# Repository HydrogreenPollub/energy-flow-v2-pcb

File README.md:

## Energy flow PCB

CADLAB preview: [link](https://cadlab.io/project/27708)

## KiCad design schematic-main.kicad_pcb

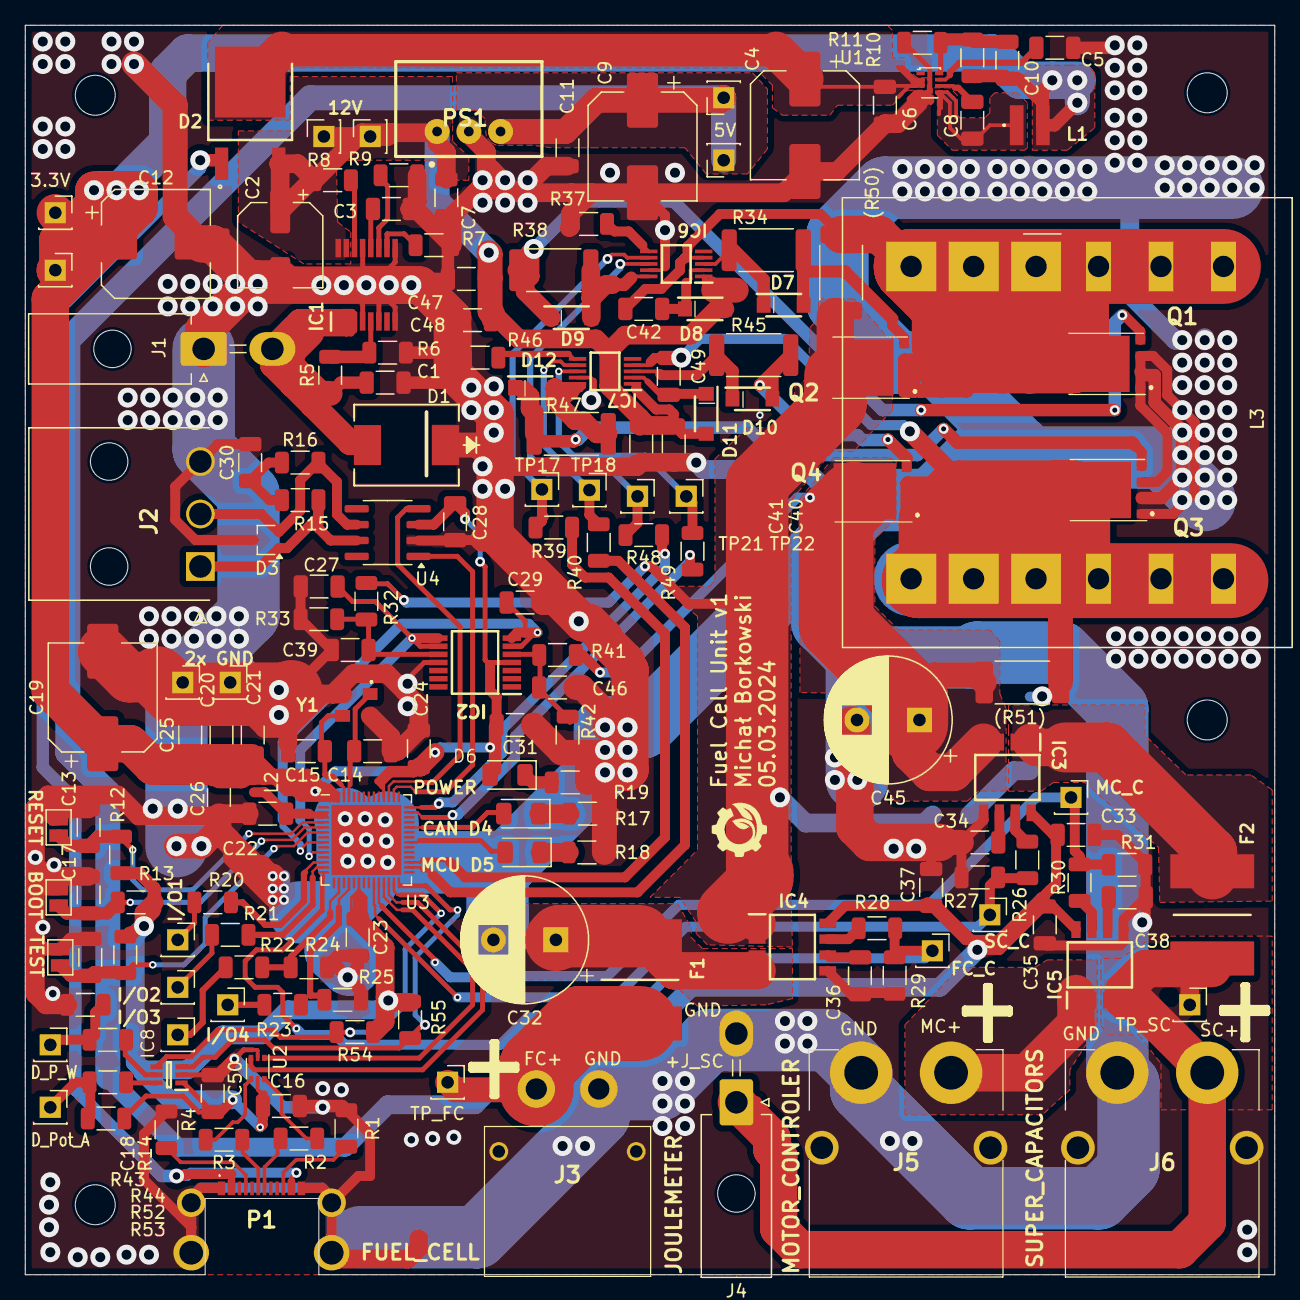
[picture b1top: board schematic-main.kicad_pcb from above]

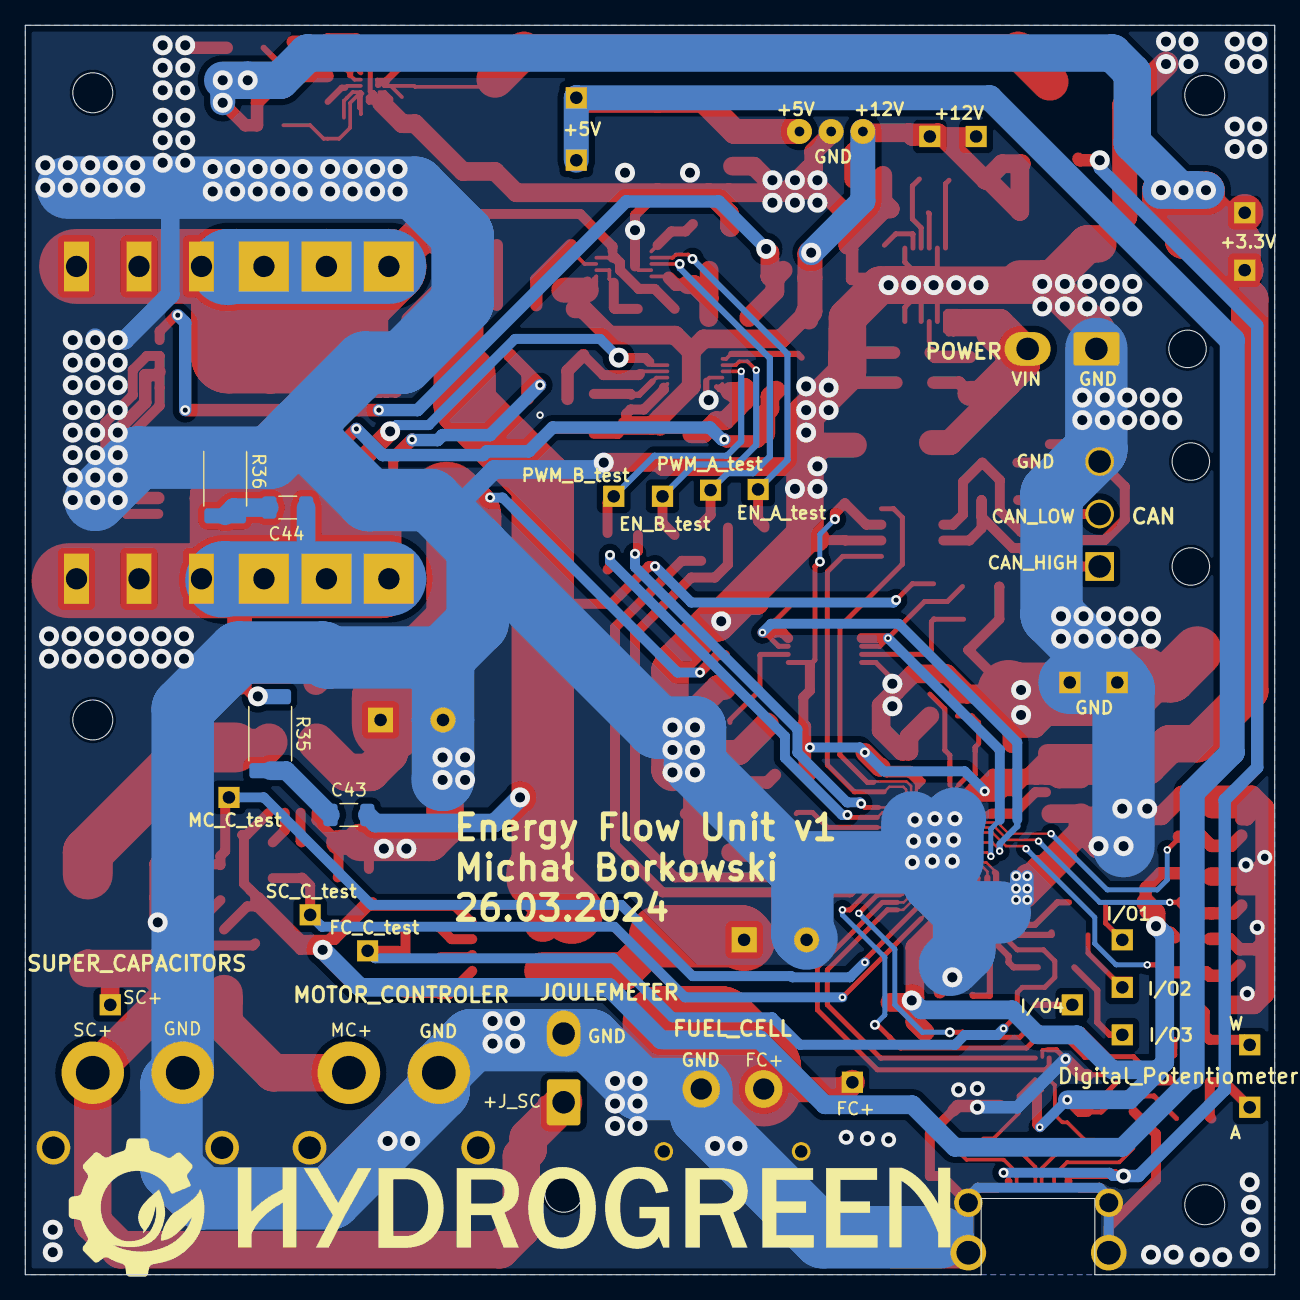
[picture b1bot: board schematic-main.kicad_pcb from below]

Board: 2 copper layers, 100.0 x 100.0 mm, 173 parts (4 on the bottom side), 96 nets.

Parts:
3.3V: +3.3V; PinSocket_1x01_P2.54mm_Vertical
5V: +5V; PinSocket_1x01_P2.54mm_Vertical
12V: +12V; PinSocket_1x01_P2.54mm_Vertical
 D6: LED; D_1206_3216Metric
(R50), (R51): 0R; R_2512_6332Metric_Pad1.40x3.35mm_HandSolder
BOOT: SolderJumper_2_Open; SolderJumper-2_P1.3mm_Open_Pad1.0x1.5mm
C1, C13, C17, C18, C20, C25: 1u; C_1206_3216Metric
C2: 47u; CP_Elec_6.3x7.7
C3: 2n7; C_1206_3216Metric
C4, C9, C19: 10u; CP_Elec_8x10.5
C5: 33n; C_1206_3216Metric
C6, C7, C8, C11, C16, C21, C22, C23, C24, C28, C31, C33, C35, C37, C50: 100n; C_1206_3216Metric
C10: 47p; C_1206_3216Metric
C12: 100u; CP_Elec_8x10.5
C14, C15: 12p; C_1206_3216Metric
C26, C41, C48: 10n; C_1206_3216Metric
C27, C29, C30: 4n7; C_1206_3216Metric
C32, C45: 100u 100V; CP_Radial_D10.0mm_P5.00mm
C34, C36, C38, C39, C46: 1n; C_1206_3216Metric
C40, C47: 470n; C_1206_3216Metric
C42, C49: 100n 100V; C_1206_3216Metric
C43, C44: 100p 100V; C_1206_3216Metric
CAN D4: LED; D_1206_3216Metric
D1: TPSMC30CA; TPSMCSeries_LTF
D2: MBRD20100CT-13; TO252_(DPAK)_1
D3: SP0502BAJT; SOT-323_SC-70
D7, D8, D9, D10, D11, D12: SKL120-AQ; SODFL3718X170N
D_P_W: D_Pot_W; PinSocket_1x01_P2.54mm_Vertical
D_Pot_A: D_Pot_A; PinSocket_1x01_P2.54mm_Vertical
F1, F2: 5A; FUSC8664X180N
FC_C: FC_C_test; PinSocket_1x01_P2.54mm_Vertical
I/O1: I/O 1; PinSocket_1x01_P2.54mm_Vertical
I/O2: I/O 2; PinSocket_1x01_P2.54mm_Vertical
I/O3: I/O 3; PinSocket_1x01_P2.54mm_Vertical
I/O4: I/O 4; PinSocket_1x01_P2.54mm_Vertical
IC1: LM76202QPWPRQ1; SOP65P640X120-17N
IC2: AD8544ARUZ-REEL; SOP65P640X120-14N
IC3, IC5: ACHS-7123-000E; SOIC127P606X204-8N
IC4: ACHS-7121-000E; SOIC127P606X204-8N
IC6, IC7: LM5106MMX_NOPB; SOP50P490X110-10N
IC8: MCP4018T-503E_LT; SOT65P210X110-6N
J1: Battery converter; Molex_Mini-Fit_Jr_5569-02A2_2x01_P4.20mm_Horizontal
J2: CAN; 39303035
J3: FUEL CELL; XT30PWF
J4: Joulemeter; Molex_Mini-Fit_Jr_5569-02A2_2x01_P4.20mm_Horizontal
J5: MOTOR CONTROLER; XT60PWM
J6: SUPER CAPACITORS; XT60PWM
L1: 4u7; SRN3015TA4R7M
L2: 2n; L_0402_1005Metric
L3: 700uH; L_Wurth_WE-HCFT-2012_LeadDiameter1.2mm
MCU D5: LED; D_1206_3216Metric
MC_C: MC_C_test; PinSocket_1x01_P2.54mm_Vertical
P1: USB_C_Plug_USB2.0; 2169900002
PS1: TSR_1-2450; TSR-1-24120
Q1, Q2, Q3, Q4: CSD19531Q5AT
R1, R4: 5k1; R_1206_3216Metric
R2, R3: 0; R_1206_3216Metric
R5: 180k; R_1206_3216Metric
R6: 12k; R_1206_3216Metric
R7, R8: 100k; R_1206_3216Metric
R9: 56k; R_1206_3216Metric
R10: 32k; R_1206_3216Metric
R11, R12, R13, R14, R24, R25, R26, R28, R30, R37, R43, R44, R46, R52, R53: 10k; R_1206_3216Metric
R15, R16: 60; R_1206_3216Metric
R17, R18, R19, R20, R21: 1k; R_1206_3216Metric
R22, R23: 100R; R_1206_3216Metric
R27, R29, R31: 20k; R_1206_3216Metric
R32: 68k; R_1206_3216Metric
R33: 3k9; R_1206_3216Metric
R34, R38, R45, R47: 10R 2W; R_2512_6332Metric
R35, R36: 100R 0,5W; R_2512_6332Metric
R39, R40, R48, R49: 200R; R_1206_3216Metric
R41: 62k; R_1206_3216Metric
R42: 4k7; R_1206_3216Metric
R54, R55: 4,7k; R_1206_3216Metric
RESET: SolderJumper_2_Open; SolderJumper-2_P1.3mm_Open_Pad1.0x1.5mm
SC_C: SC_C_test; PinSocket_1x01_P2.54mm_Vertical
TEST: SolderJumper_2_Open; SolderJumper-2_P1.3mm_Open_Pad1.0x1.5mm
TP1, TP2: GND; PinSocket_1x01_P2.54mm_Vertical
TP3: +12V; PinSocket_1x01_P2.54mm_Vertical
TP5: +5V; PinSocket_1x01_P2.54mm_Vertical
TP8: +3.3V; PinSocket_1x01_P2.54mm_Vertical
TP17: EN A test; PinSocket_1x01_P2.54mm_Vertical
TP18: PWM A test; PinSocket_1x01_P2.54mm_Vertical
TP21: EN B test; PinSocket_1x01_P2.54mm_Vertical
TP22: PWM B test; PinSocket_1x01_P2.54mm_Vertical
TP_FC: FC test; PinSocket_1x01_P2.54mm_Vertical
TP_SC: SC test; PinSocket_1x01_P2.54mm_Vertical
U1: TPS62933; SOT-583-8
U2: USBLC6-2P6; SOT-666
U3: ESP32-S3FN8; QFN-56-1EP_7x7mm_P0.4mm_EP5.6x5.6mm
U4: SN65HVD232; SOIC-8_3.9x4.9mm_P1.27mm
Y1: Crystal_GND24; KC3225K400000C1GE00

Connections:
+3.3V: 3.3V.1, D6.2 (A), C10.1, C12.1, C16.1, C19.1, C20.1, C21.1, C23.1, C24.1, C25.1, C26.1, C28.1, C31.1, C50.1, IC2.4 (V+), IC8.1 (VDD), L1.2, L2.1, R10.1, R12.2, R13.2, R14.2, R53.1, R54.1, R55.1, TP8.1, U2.5 (VBUS), U3.20 (VDD3P3_RTC), U3.46 (VDD3P3_CPU), U3.55 (VDDA), U3.56 (VDDA), U4.3 (VCC)
+5V: 5V.1, C9.1, C11.1, C33.1, C35.1, C37.1, IC3.8 (VDD), IC4.8 (VDD), IC5.8 (VDD), PS1.3 (VOUT+), TP5.1
+12V: 12V.1, C2.1, C7.1, C40.1, C41.1, C47.1, C48.1, D2.2, D8.2 (A), D11.2 (A), IC1.15 (OUT_1), IC1.16 (OUT_2), IC6.1 (VDD), IC7.1 (VDD), PS1.1 (VIN+), R8.1, TP3.1
/Converter/Bootstrap_A: (R50).2, C42.2, IC6.4 (HS), L3.1, Q1.5 (D_1), Q1.6 (D_2), Q1.7 (D_3), Q1.8 (D_4), Q1.9 (D_5), Q2.1 (S_1), Q2.2 (S_2), Q2.3 (S_3)
/Converter/Bootstrap_B: (R51).1, C44.1, C49.2, IC7.4 (HS), L3.2, Q3.5 (D_1), Q3.6 (D_2), Q3.7 (D_3), Q3.8 (D_4), Q3.9 (D_5), Q4.1 (S_1), Q4.2 (S_2), Q4.3 (S_3), R35.1
/Converter/Converter_ON_A_MCU: R39.1, U3.31 (SPIWP/GPIO28)
/Converter/Converter_ON_B_MCU: R48.1, U3.42 (GPIO37)
/Converter/Converter_PWM_A_MCU: R40.2, U3.30 (SPIHD/GPIO27)
/Converter/Converter_PWM_B_MCU: R49.2, U3.41 (GPIO36)
/Converter/FC+: F1.1, J3.2, TP_FC.1
/Converter/FC_V: C39.1, IC2.10 (+IN_C), R32.1, R33.2
/Converter/FC_c1: C32.1, F1.2, IC4.3 (IP-_1), IC4.4 (IP-_2)
/Converter/FC_c2: (R50).1, C43.1, IC4.1 (IP+_1), IC4.2 (IP+_2), Q2.5 (D_1), Q2.6 (D_2), Q2.7 (D_3), Q2.8 (D_4), Q2.9 (D_5), R32.2
/Converter/FC_c_MCU: FC_C.1, R28.1, R29.2, U3.14 (GPIO9/ADC1_CH8)
/Converter/High_mosfet_A: D7.2 (A), Q2.4 (G), R34.2
/Converter/High_mosfet_B: D10.2 (A), Q4.4 (G), R45.2
/Converter/Low_mosfet_A: D9.1 (K), Q1.4 (G), R38.1
/Converter/Low_mosfet_B: D12.1 (K), Q3.4 (G), R47.1
/Converter/MC_c1: F2.1, IC5.3 (IP-_1), IC5.4 (IP-_2), J4.1, J6.1, TP_SC.1
/Converter/MC_c2: IC5.1 (IP+_1), IC5.2 (IP+_2), J5.1
/Converter/MC_c_MCU: MC_C.1, R30.1, R31.2, U3.24 (GPIO18/ADC2_CH7)
/Converter/SC_V: C46.1, IC2.5 (+IN_B), R41.1, R42.2
/Converter/SC_c1: (R51).2, C45.1, IC3.3 (IP-_1), IC3.4 (IP-_2), Q4.5 (D_1), Q4.6 (D_2), Q4.7 (D_3), Q4.8 (D_4), Q4.9 (D_5), R41.2
/Converter/SC_c2: F2.2, IC3.1 (IP+_1), IC3.2 (IP+_2)
/Converter/SC_c_MCU: R26.1, R27.2, SC_C.1, U3.23 (GPIO17/ADC2_CH6)
/IO/CANH: D3.1 (K), J2.1, R15.2, U4.7 (CANH)
/IO/CANL: D3.2 (K), J2.2, R16.2, U4.6 (CANL)
/IO/CAN_RX: U3.44 (MTCK/JTAG/GPIO39), U4.1 (D)
/IO/CAN_TX: U3.45 (MTDO/JTAG/GPIO40), U4.4 (R)
/IO/FC_Voltage_MCU: C27.1, IC2.8 (OUT_C), IC2.9 (-IN_C), U3.10 (GPIO5/ADC1_CH4)
/IO/I/O_1_MCU: R20.2, U3.12 (GPIO7/ADC1_CH6)
/IO/I/O_2_MCU: R21.2, U3.13 (GPIO8/ADC1_CH7)
/IO/I/O_3_MCU: R22.2, R24.1, U3.16 (GPIO11/ADC2_CH0)
/IO/I/O_4_MCU: R23.2, R25.1, U3.18 (GPIO13/ADC2_CH2)
/IO/LED_CAN_STATUS: CAN D4.2 (A), U3.38 (GPIO33)
/IO/LED_MCU_STATUS: MCU D5.2 (A), U3.35 (SPID/GPIO32)
/IO/SCL_D_Pot_i2c_MCU: IC8.3 (SCL), R55.2, U3.28 (SPI_CS1/GPIO26)
/IO/SC_Voltage_MCU: C29.1, IC2.6 (-IN_B), IC2.7 (OUT_B), U3.8 (GPIO3/ADC1_CH2)
/IO/SDA_D_Pot_i2c_MCU: IC8.4 (SDA), R54.2, U3.27 (GPIO21)
/MCU/BOOT: BOOT.1 (A), C17.1, R13.1, U3.5 (GPIO0/BOOT)
/MCU/MCU_TEST: C18.1, R14.1, TEST.1 (A), U3.6 (GPIO1/ADC1_CH0)
/MCU/RESET: C13.1, R12.1, RESET.1 (A), U3.4 (CHIP_PU/RESET)
/MCU/USB_D+: R3.2, U2.3 (I/O2), U2.4 (I/O2), U3.26 (GPIO20/USB_D+/ADC2_CH9)
/MCU/USB_D-: R2.2, U2.1 (I/O1), U2.6 (I/O1), U3.25 (GPIO19/USB_D-/ADC2_CH8)
/MCU/XTAL_N: C14.1, U3.53 (XTAL_N), Y1.1
/MCU/XTAL_P: C15.1, U3.54 (XTAL_P), Y1.3
/Power /Vin: C1.1, D1.2 (A), IC1.1 (IN_1), IC1.2 (IN_2), IC1.3 (UVLO), J1.2, R5.1
/VBUS: D2.1, P1.A4 (VBUS), P1.A9 (VBUS), P1.B4 (VBUS), P1.B9 (VBUS)
GND: BOOT.2 (B), C1.2, C2.2, C3.2, C4.2, C5.2, C6.2, C7.2, C9.2, C11.2, C12.2, C13.2, C14.2, C15.2, C16.2, C17.2, C18.2, C19.2, C20.2, C21.2, C22.2, C23.2, C24.2, C25.2, C26.2, C27.2, C28.2, C29.2, C30.2, C31.2, C32.2, C33.2, C34.2, C35.2, C36.2, C37.2, C38.2, C39.2, C40.2, C41.2, C45.2, C46.2, C47.2, C48.2, C50.2, D1.1 (K), D3.3 (A), IC1.4 (NC_1), IC1.6 (MODE), IC1.8 (RTN), IC1.9 (GND), IC1.13 (NC_2), IC1.17 (EP), IC2.11 (GND), IC3.5 (GND), IC4.5 (GND), IC5.5 (GND), IC6.9 (VSS), IC7.9 (VSS), IC8.2 (VSS), J1.1, J2.3, J3.1, J4.2, J5.2, J6.2, P1.A1 (GND), P1.A12 (GND), P1.B1 (GND), P1.B12 (GND), PS1.2 (GND), Q1.1 (S_1), Q1.2 (S_2), Q1.3 (S_3), Q3.1 (S_1), Q3.2 (S_2), Q3.3 (S_3), R1.2, R4.2, R6.2, R7.2, R9.2, R11.2, R17.2, R18.2, R19.2, R24.2, R25.2, R27.1, R29.1, R31.1, R33.1, R36.1, R37.1, R42.1, R43.2, R46.1, RESET.2 (B), TEST.2 (B), TP1.1, TP2.1, U1.4 (GND), U2.2 (GND), U3.57 (GND), U4.2 (GND), Y1.2, Y1.4
unnamed: C30.1, R15.1, R16.1
unnamed: C43.2, R35.2
unnamed: C44.2, R36.2
unnamed: CAN D4.1 (K), R17.1
unnamed: MCU D5.1 (K), R18.1
unnamed: D6.1 (K), R19.1
unnamed: D7.1 (K), IC6.3 (HO), R34.1
unnamed: C42.1, D8.1 (K), IC6.2 (HB)
unnamed: D9.2 (A), IC6.10 (LO), R38.2
unnamed: D10.1 (K), IC7.3 (HO), R45.1
unnamed: C49.1, D11.1 (K), IC7.2 (HB)
unnamed: D12.2 (A), IC7.10 (LO), R47.2
unnamed: C3.1, IC1.12 (DVDT)
unnamed: IC1.11 (ILIM), R9.1
unnamed: IC1.10 (IMON), R7.1
unnamed: IC1.5 (OVP), R5.2, R6.1
unnamed: IC1.14 (~FLT), R8.2
unnamed: C34.1, IC3.6 (FILTER)
unnamed: IC3.7 (VOUT), R26.2
unnamed: C36.1, IC4.6 (FILTER)
unnamed: IC4.7 (VOUT), R28.2
unnamed: C38.1, IC5.6 (FILTER)
unnamed: IC5.7 (VOUT), R30.2
unnamed: IC6.7 (EN), R39.2, TP17.1
unnamed: IC6.8 (IN), R40.1, TP18.1
unnamed: IC6.6 (RDT), R37.2
unnamed: IC7.7 (EN), R48.2, TP21.1
unnamed: IC7.8 (IN), R49.1, TP22.1
unnamed: IC7.6 (RDT), R46.2
unnamed: IC8.6 (A), R52.2
unnamed: IC8.5 (W), R44.1
unnamed: P1.A5 (CC), R4.1
unnamed: P1.A6 (D+), R3.1
unnamed: P1.A7 (D-), R2.1
unnamed: P1.B5 (VCONN), R1.1
unnamed: I/O1.1, R20.1
unnamed: I/O2.1, R21.1
unnamed: I/O3.1, R22.1
unnamed: I/O4.1, R23.1
unnamed: D_P_W.1, R43.1, R44.2
unnamed: D_Pot_A.1, R52.1, R53.2
unnamed: C8.1, U1.6 (BST)
unnamed: C10.2, R10.2, R11.1, U1.8 (FB)
unnamed: C5.1, U1.7 (SS)
unnamed: C8.2, L1.1, U1.5 (SW)
unnamed: C4.1, C6.1, D2.3, U1.3 (VIN)
VDD3P3: C22.1, L2.2, U3.2 (VDD3P3), U3.3 (VDD3P3)

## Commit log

2024-01-27 First converter version
2024-01-31 Resend
2024-01-31 Backlink to CADLAB.io has been added.
2024-02-02 Repair files
2024-02-07 Add test points
2024-02-07 Edit mosfets outputs
2024-02-26 Update README.md with CADLAB link
2024-02-26 First pcb
2024-03-12 Buck - boost converter
2024-03-21 Add coil and microcontroler
2024-03-23 Add pot
2024-03-24 PCB design 50%
2024-03-24 PCB design 80%
2024-03-26 PCB design complate
2024-03-28 Logs
2024-03-30 Labels
2024-03-30 DRC Tested
2024-04-05 Rename and send to production
